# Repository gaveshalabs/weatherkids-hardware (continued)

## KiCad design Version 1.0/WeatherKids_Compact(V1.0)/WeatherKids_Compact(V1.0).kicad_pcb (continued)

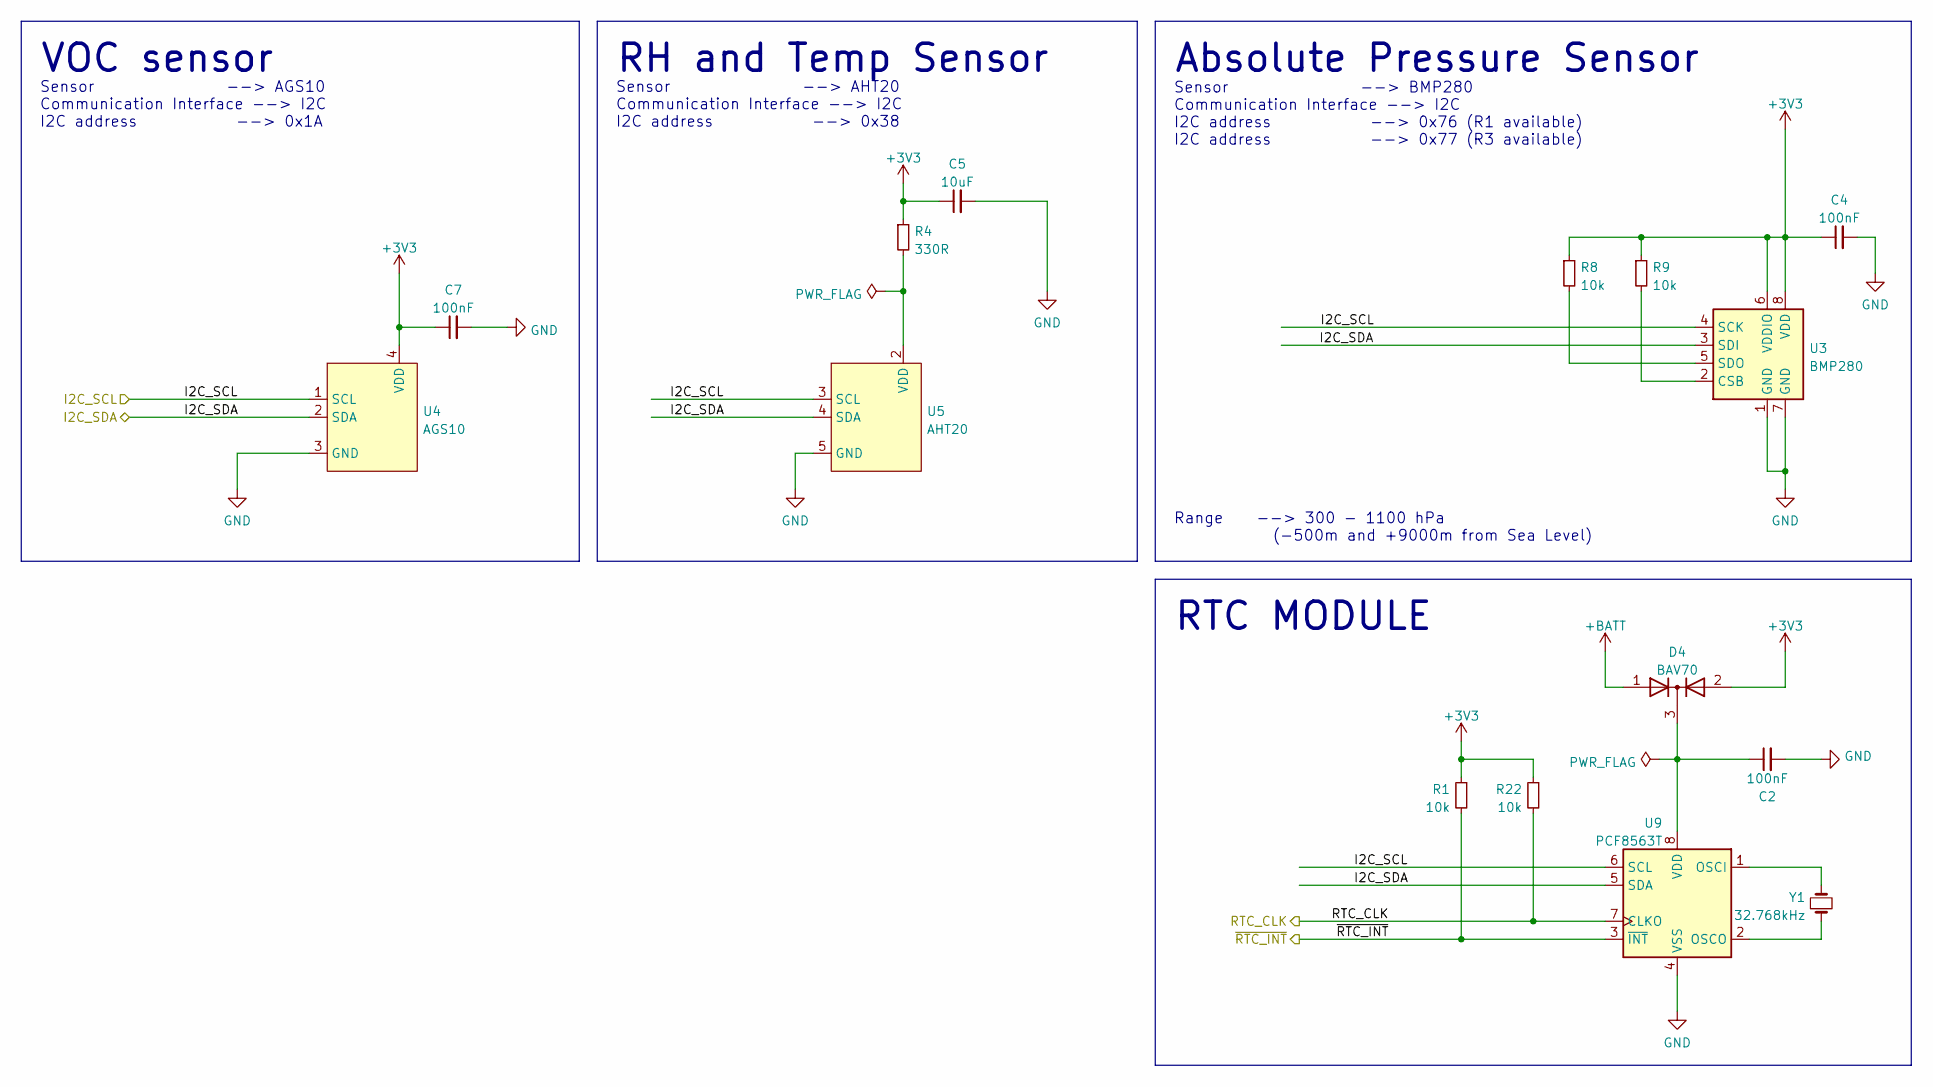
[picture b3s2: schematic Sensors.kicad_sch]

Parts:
C2, C4, C7: 100nF; C_0402_1005Metric
C5: 10uF; C_0805_2012Metric
D4: BAV70; SOT-23
R1, R8, R9, R22: 10k; R_0402_1005Metric
R4: 330R; R_0402_1005Metric
U3: BMP280; Bosch_LGA-8_2x2.5mm_P0.65mm_ClockwisePinNumbering
U4: AGS10
U5: AHT20
U9: PCF8563T; SOIC-8_3.9x4.9mm_P1.27mm
Y1: 32.768kHz; Crystal_SMD_3215-2Pin_3.2x1.5mm

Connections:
+3V3: C4.1, C5.1, C7.1, D4.2 (A), R1.1, R4.1, R8.1, R9.1, R22.1, U3.6 (VDDIO), U3.8 (VDD), U4.4 (VDD); also elsewhere on the board
+BATT: D4.1 (A); also elsewhere on the board
/Environment Sensors/RTC_CLK: R22.2, U9.7 (CLKO); also elsewhere on the board
/Environment Sensors/~RTC_INT: R1.2, U9.3 (~INT); also elsewhere on the board
/I2C_SCL: U3.4 (SCK), U4.1 (SCL), U5.3 (SCL), U9.6 (SCL); also elsewhere on the board
/I2C_SDA: U3.3 (SDI), U4.2 (SDA), U5.4 (SDA), U9.5 (SDA); also elsewhere on the board
GND: C2.2, C4.2, C5.2, C7.2, U3.1 (GND), U3.7 (GND), U4.3 (GND), U5.5 (GND), U9.4 (VSS); also elsewhere on the board
unnamed: C2.1, D4.3 (K), U9.8 (VDD)
unnamed: R4.2, U5.2 (VDD)
unnamed: R8.2, U3.5 (SDO)
unnamed: R9.2, U3.2 (CSB)
unnamed: U9.1 (OSCI), Y1.2
unnamed: U9.2 (OSCO), Y1.1

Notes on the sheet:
Sensor --> AGS10 Communication Interface --> I2C I2C address --> 0x1A
Sensor --> BMP280 Communication Interface --> I2C I2C address --> 0x76 (R1 available) I2C address --> 0x77 (R3 available)
Range --> 300 - 1100 hPa (-500m and +9000m from Sea Level)
RH and Temp Sensor
RTC MODULE
Sensor --> AHT20 Communication Interface --> I2C I2C address --> 0x38
VOC sensor
Absolute Pressure Sensor

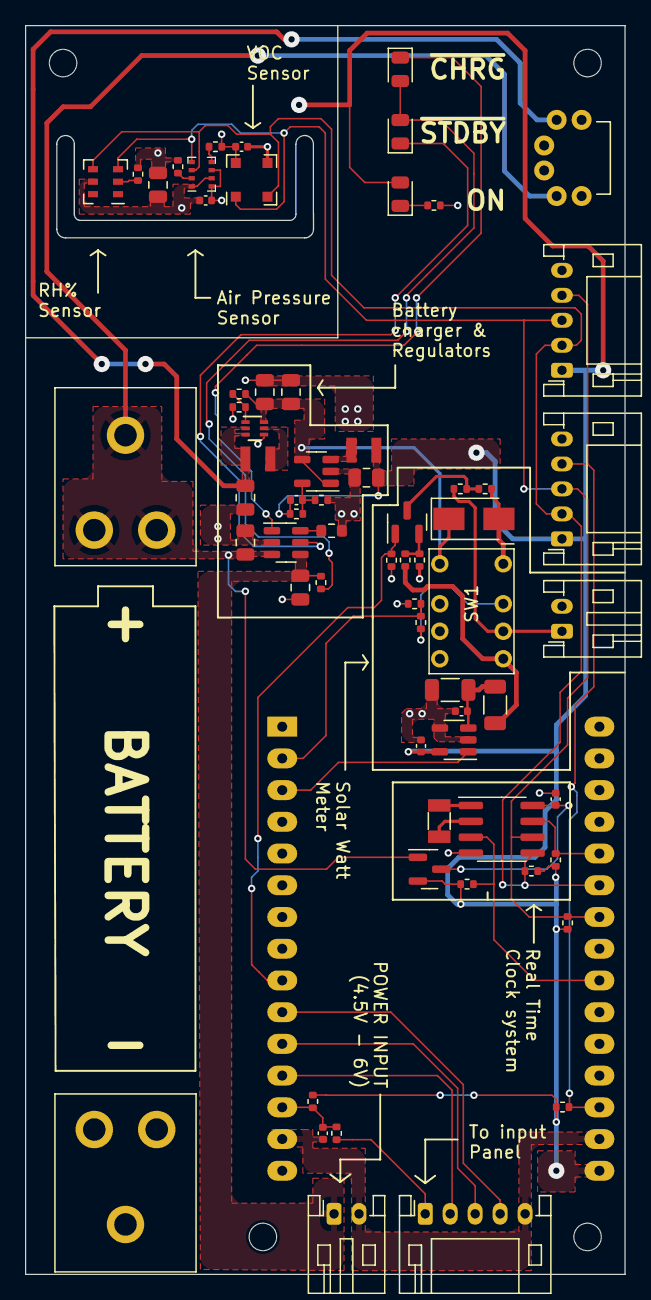
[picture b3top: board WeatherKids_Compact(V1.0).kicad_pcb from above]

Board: 2 copper layers, 48.0 x 100.0 mm, 71 parts (0 on the bottom side), 41 nets.

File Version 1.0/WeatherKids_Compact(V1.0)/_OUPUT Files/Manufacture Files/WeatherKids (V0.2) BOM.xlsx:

Index | Availability | Checked | Layer | Special Notes |  | Value | Footprint |  | JLC Basic Part Match | JLCPCBA part | LCSC Part Number | Manufacturer Part Number | Manufacture | Unit Price | Total
1 | YES |  |  |  | C2, C3, C4, C6, C7, C9 | 100nF | Capacitor_SMD:C_0402_1005Metric | 6 | Y | C1525 | C60474 | CC0402KRX7R7BB104 |  | 8.0000000000000004E-4 | 4.8000000000000004E-3
2 | YES |  |  |  | C10 | 12pF | Capacitor_SMD:C_0402_1005Metric | 1 | Y | C1547 | C106201 | CC0402JRNPO9BN120 |  | 1E-3 | 1E-3
3 | YES |  |  |  | C5, C8, C11, C12, C13, C15, C16 | 10uF | Capacitor_SMD:C_0805_2012Metric | 7 | Y | C15850 | C89827 | CC0805KKX5R7BB106 |  | 2.75E-2 | 0.1925
4 | YES |  |  |  | D6 | SS34 | Diode_SMD:D_SMA | 1 | Y | C8678 | C8678 | SS34 |  | 2.7799999999999998E-2 | 2.7799999999999998E-2
5 | YES |  |  |  | D4 | BAV70 | Package_TO_SOT_SMD:SOT-23 | 1 | Y | C68978 | C68978 | BAV70 |  | 1.8499999999999999E-2 | 1.8499999999999999E-2
6 | YES |  |  |  | D1, D2, D5 | LED | LED_SMD:LED_0805_2012Metric | 3 | Y | C34499 | C34499 | C34499 | Hubei KENTO Elec | 1.5699999999999999E-2 | 4.7099999999999996E-2
7 | YES |  |  |  | J1, J2, J3 | Conn_01x05 | Connector_JST:JST_PH_S5B-PH-K_1x05_P2.00mm_Horizontal | 3 | N | C10402 | C442192 | HX20007-5WAD |  | 3.0499999999999999E-2 | 9.1499999999999998E-2
8 | YES |  |  |  | J4, J5 | Conn_01x02 | Connector_JST:JST_PH_S2B-PH-K_1x02_P2.00mm_Horizontal | 2 | N | C16965 | C16965 | PH-2AW |  | 5.5999999999999999E-3 | 1.12E-2
 | YES |  |  |  | J6, J7 | CONN1X15 | 2.54 Female connector | 2 | N | C124408 | C124408 | B-2200S15P-A120 |  | 0.15179999999999999 | 0.30359999999999998
9 | YES |  |  |  | J9, J10 | MY-18650-01 | Myoung:MY-18650-01 | 2 | N | C2979183 | C2979183 | MY-18650-01 |  | 0.30520000000000003 | 0.61040000000000005
10 | YES |  |  |  | L1 | 1uH | Inductor_SMD:L_Taiyo-Yuden_NR-20xx | 1 | N | C279952 | C279952 | WPN252010U1R0MT |  | 5.7200000000000001E-2 | 5.7200000000000001E-2
11 | YES |  |  |  | L2 | 2.2uH | Sunlord Inductors:WPN252010U | 1 | N | C279871 | C279871 | WPN252010U2R2MT |  | 5.1700000000000003E-2 | 5.1700000000000003E-2
12 | YES |  |  |  | Q1 | AO3400A | Package_TO_SOT_SMD:SOT-23 | 1 | Y | C20917 | C20917 | AO3400A |  | 7.9000000000000001E-2 | 7.9000000000000001E-2
13 | YES |  |  |  | R2 | 1R | Resistor_SMD:R_1206_3216Metric | 1 | Y | C17928 | C17928 | 1206W4F100KT5E |  | 4.4000000000000003E-3 | 4.4000000000000003E-3
14 | YES |  |  |  | R4, R14, R25 | 330R | Resistor_SMD:R_0402_1005Metric | 1 | Y | C25104 | C25104 | 0402WGF3300TCE |  | 5.0000000000000001E-4 | 5.0000000000000001E-4
15 | YES |  |  |  | R5, R23, R24 | 4.7k | Resistor_SMD:R_0402_1005Metric | 3 | Y | C25900 | C25900 | 0402WGF4701TCE |  | 5.9999999999999995E-4 | 1.8E-3
16 | YES |  |  |  | R3, R6, R7, R10 | 0R | Resistor_SMD:R_0402_1005Metric | 4 | Y | C17168 | C17168 | 0402WGF0000TCE |  | 5.0000000000000001E-4 | 2E-3
17 | YES |  |  |  | R1, R8, R9, R11, R15, R22 | 10k | Resistor_SMD:R_0402_1005Metric | 6 | Y | C25744 | C60490 | RC0402FR-0710KL |  | 5.0000000000000001E-4 | 3.0000000000000001E-3
18 | YES |  |  |  | R16 | 1k | Resistor_SMD:R_0402_1005Metric | 1 | Y | C11702 | C11702 | 0402WGF1001TCE |  | 5.0000000000000001E-4 | 5.0000000000000001E-4
19 | YES |  |  |  | R17 | 2k | Resistor_SMD:R_0603_1608Metric | 1 | y | C4109 | C4109 | 0402WGF2001TCE |  | 5.0000000000000001E-4 | 5.0000000000000001E-4
20 | YES |  |  |  | R12, R13, R18 | 100k | Resistor_SMD:R_0402_1005Metric | 3 | y | C25741 | C25741 | 0402WGF1003TCE |  | 5.0000000000000001E-4 | 1.5E-3
21 | YES |  |  |  | R19 | 510k | Resistor_SMD:R_0402_1005Metric | 1 | y | C11616 | C11616 | 0402WGF5103TCE |  | 5.9999999999999995E-4 | 5.9999999999999995E-4
22 | YES |  |  |  | R20 | 22k | Resistor_SMD:R_0402_1005Metric | 1 | Y | C25768 | C25768 | 0402WGF2202TCE |  | 5.0000000000000001E-4 | 5.0000000000000001E-4
23 | YES |  |  |  | R26 | 100R | Resistor_SMD:R_1206_3216Metric | 1 | Y | C17901 | C17901 | 1206W4F1000T5E |  | 2.8999999999999998E-3 | 2.8999999999999998E-3
24 | YES |  |  |  | R21 | 68k | Resistor_SMD:R_0402_1005Metric | 1 | y | C36871 | C36871 | 0402WGF6802TCE |  | 5.9999999999999995E-4 | 5.9999999999999995E-4
25 | YES |  |  |  | SW1 | HFD4_5S | Xiamen_Hiongfa:HDF4 | 1 | N | C23510 | C23510 | HFD4/5 |  | 1.0077 | 1.0077
26 | YES |  |  |  | SW2 | SW_SPST | XKB:XKB5858-X-E | 1 | N | C780038 | C780038 | XKB5858-Z-E |  | 0.21479999999999999 | 0.21479999999999999
27 | YES |  |  |  | U2 | INA180A2 | Package_TO_SOT_SMD:SOT-23-5 | 1 | N | C192764 | C192764 | INA180A2IDBVR |  | 0.25740000000000002 | 0.25740000000000002
28 | YES |  |  |  | U3 | BMP280 | Package_LGA:Bosch_LGA-8_2x2.5mm_P0.65mm_ClockwisePinNumbering | 1 | N | C83291 | C83291 | BMP280 |  | 1.5547 | 1.5547
29 | YES |  |  |  | U4 | AGS10 | ASAIR Sensors:AGS10 | 1 | N | C3012632 | C3012632 | AGS10 |  | 1.4497 | 1.4497
30 | YES |  |  |  | U5 | AHT20 | ASAIR Sensors:AHT20 | 1 | N | C3012622 | C3012622 | AHT20-F |  | 0.70369999999999999 | 0.70369999999999999
31 | YES |  |  |  | U6 | TP4057 | Package_TO_SOT_SMD:SOT-23-6 | 1 | N | C12044 | C12044 | TP4057-42-SOT26-R |  | 0.12809999999999999 | 0.12809999999999999
32 | YES |  |  |  | U7 | RT8059GJ5 | Package_TO_SOT_SMD:TSOT-23-5 | 1 | N | C20542 | C20542 | RT5796CHGJ5 |  | 0.2 | 0.2
33 | YES |  |  |  | U1 | TPS61023DRL | Texas_Instruments:DRL0006A | 1 | N | C919459 | C919459 | TPS61023DRLR |  | 0.27700000000000002 | 0.27700000000000002
34 | YES |  |  |  | U9 | PCF8563T | Package_SO:SOIC-8_3.9x4.9mm_P1.27mm | 1 | Y | C7440 | C7440 | PCF8563T/5,518 |  | 0.5877 | 0.5877
35 | YES |  |  |  | Y1 | 32.768kHz | Crystal:Crystal_SMD_3215-2Pin_3.2x1.5mm | 1 | Y | C32346 | C32346 | Q13FC1350000400 |  | 0.1978 | 0.1978
36 | YES |  | NA | ESP32 DevKit | MOD1 | ESP32_DEVKIT_V1 | Espressif_Systems:ESP32_DEVKIT_V1.0 | 1 | N |  |  | ESP32_DEVKIT_V1 |  | 3.9473684210526314 | 3.9473684210526314
37 | YES |  | NA | 1800 mAh Batter | Battery | Batttery | Li-ion battery | 1 | N |  |  | Batttery |  | 1.5 | 1.5
38 | YES |  | NA | 2 Layer PCB Cost | PCB |  |  | 1 | N |  |  |  |  | 0.51 | 0.51
39 | YES |  | NA | Soldering (single side) | Assembly Fee |  |  | 1 | N |  |  |  |  | 2.2999999999999998 | 2.2999999999999998
40 | YES |  | NA | 3D printed casing | Casing |  |  | 1 | N |  |  |  |  | 3 | 3
41 | YES |  | NA | Shipping cost from china to Sri Lanka | Direct Shipping cost |  |  | 1 | N |  |  |  |  | 3.5 | 3.5
42 | YES |  |  |  | H1-H4 | Screws |  | 4 | N
 |  |  |  |  |  |  |  |  |  |  |  |  | Total without Tax |  | 22.851068421052631
 |  |  |  |  |  |  |  |  |  |  |  |  | Total with Tax |  | 24.679153894736842
 |  |  |  |  |  |  |  |  |  |  |  |  | Total with 10% error Margine |  | 27.147069284210527
 |  |  |  |  |  |  |  |  |  |  |  |  | Final Cost (LKR) |  | 10315.886328000001

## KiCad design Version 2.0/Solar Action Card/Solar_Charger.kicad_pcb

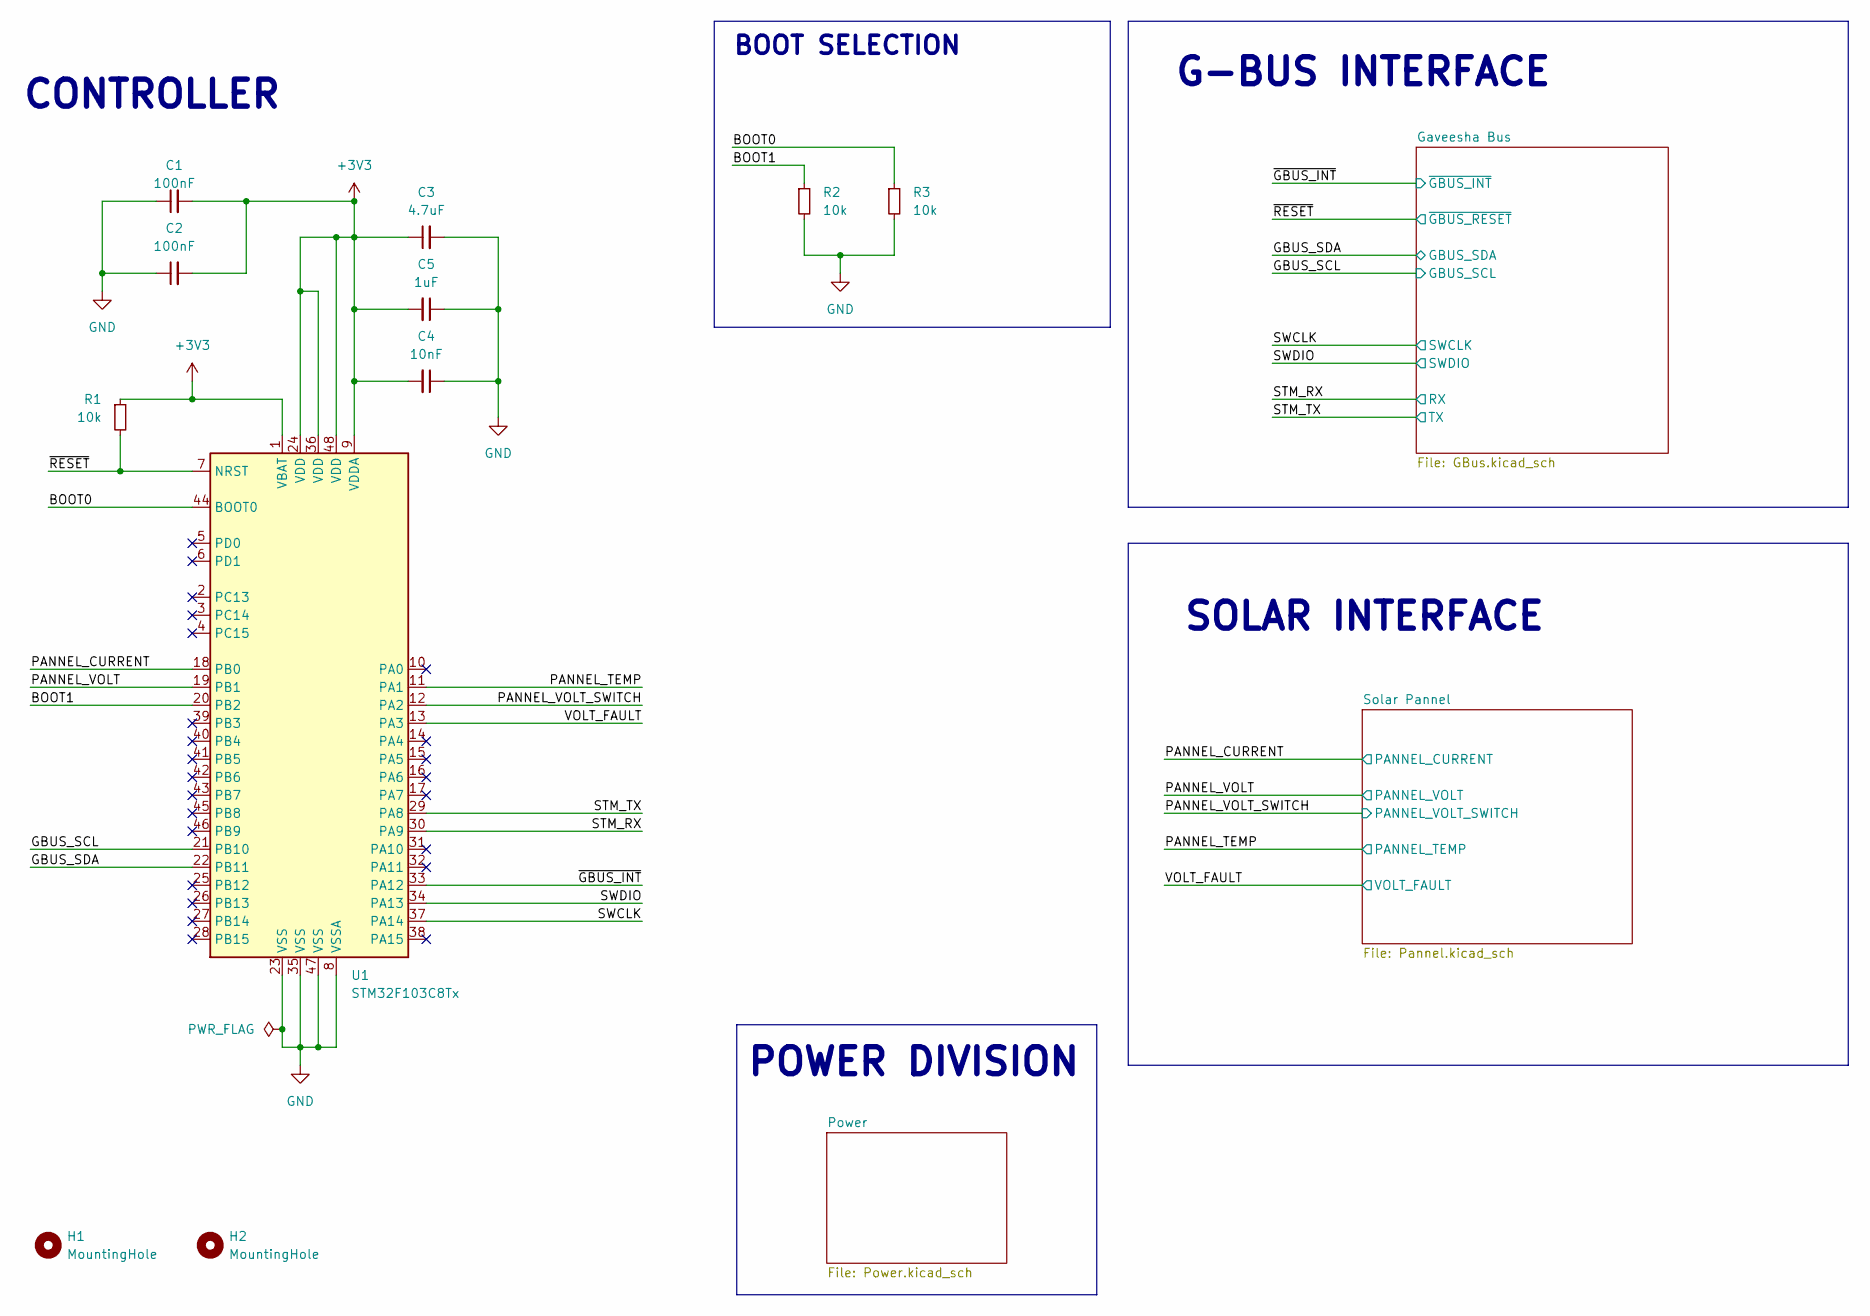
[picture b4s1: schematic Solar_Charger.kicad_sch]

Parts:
C1, C2: 100nF; C_0603_1608Metric; JLC PCB Part No. C1525
C3: 4.7uF; C_0402_1005Metric; JLC PCB Part No C23733
C4: 10nF; C_0402_1005Metric; JLC PCB Part No. C15195
C5: 1uF; C_0402_1005Metric; JLC PCB Part No. C52923
H1, H2: MountingHole; MountingHole_2.2mm_M2
R1, R2, R3: 10k; R_0402_1005Metric
U1: STM32F103C8Tx; LQFP-48_7x7mm_P0.5mm

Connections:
+3V3: C1.2, C2.2, C3.1, C4.2, C5.2, R1.1, U1.1 (VBAT), U1.9 (VDDA), U1.24 (VDD), U1.36 (VDD), U1.48 (VDD); also elsewhere on the board
/BOOT0: R3.1, U1.44 (BOOT0)
/BOOT1: R2.1, U1.20 (PB2)
/GBUS_SCL: U1.21 (PB10); also elsewhere on the board
/GBUS_SDA: U1.22 (PB11); also elsewhere on the board
/PANNEL_CURRENT: U1.18 (PB0); also elsewhere on the board
/PANNEL_TEMP: U1.11 (PA1); also elsewhere on the board
/PANNEL_VOLT: U1.19 (PB1); also elsewhere on the board
/PANNEL_VOLT_SWITCH: U1.12 (PA2); also elsewhere on the board
/STM_RX: U1.30 (PA9); also elsewhere on the board
/STM_TX: U1.29 (PA8); also elsewhere on the board
/SWCLK: U1.37 (PA14); also elsewhere on the board
/SWDIO: U1.34 (PA13); also elsewhere on the board
/VOLT_FAULT: U1.13 (PA3); also elsewhere on the board
/~GBUS_INT: U1.33 (PA12); also elsewhere on the board
/~RESET: R1.2, U1.7 (NRST); also elsewhere on the board
GND: C1.1, C2.1, C3.2, C4.1, C5.1, R2.2, R3.2, U1.8 (VSSA), U1.23 (VSS), U1.35 (VSS), U1.47 (VSS); also elsewhere on the board

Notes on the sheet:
CONTROLLER
BOOT SELECTION
POWER DIVISION
SOLAR INTERFACE
G-BUS INTERFACE

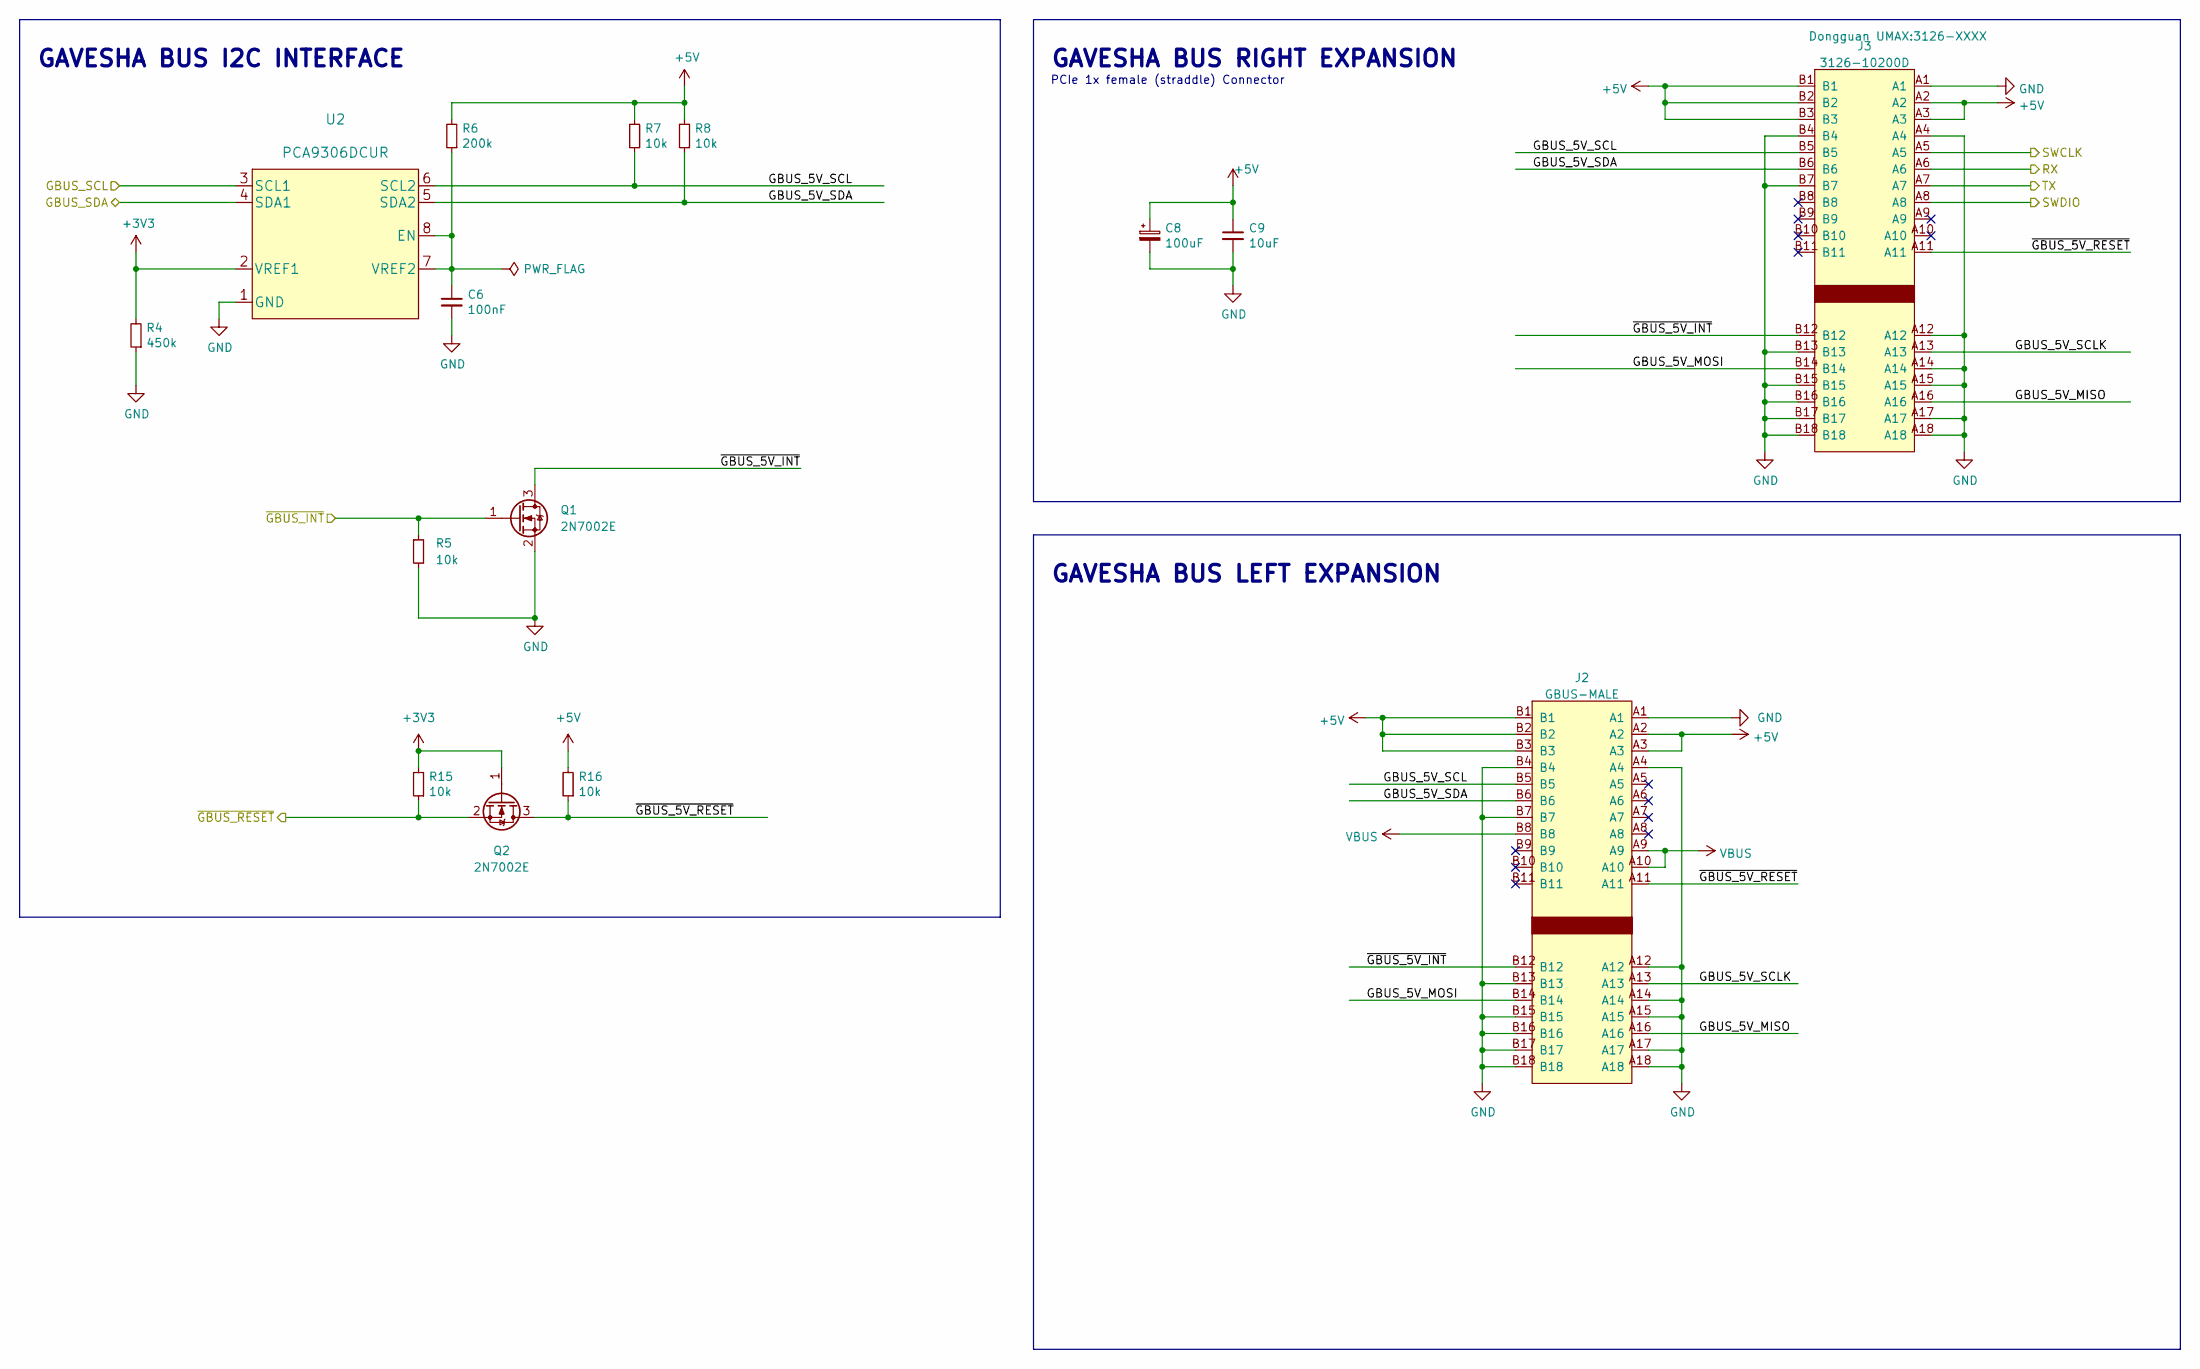
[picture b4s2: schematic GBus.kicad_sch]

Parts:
C6: 100nF; C_0402_1005Metric
C8: 100uF; CP_EIA-3528-12_Kemet-T
C9: 10uF; C_0805_2012Metric
J2: GBUS-MALE; GBUS_MALE
J3: 3126-10200D; 3126-XXXX
Q1, Q2: 2N7002E; SOT-23
R4: 450k; R_0402_1005Metric
R5, R7, R8, R15, R16: 10k; R_0402_1005Metric
R6: 200k; R_0402_1005Metric
U2: PCA9306DCUR

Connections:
+3V3: Q2.1 (G), R4.2, R15.2, U2.2 (VREF1); also elsewhere on the board
+5V: C8.1, C9.1, J2.A2, J2.A3, J2.B1, J2.B2, J2.B3, J3.A2, J3.A3, J3.B1, J3.B2, J3.B3, R6.2, R7.2, R8.2, R16.2; also elsewhere on the board
/GBUS_SCL: U2.3 (SCL1); also elsewhere on the board
/GBUS_SDA: U2.4 (SDA1); also elsewhere on the board
/Gaveesha Bus/GBUS_5V_MISO: J2.A16, J3.A16
/Gaveesha Bus/GBUS_5V_MOSI: J2.B14, J3.B14
/Gaveesha Bus/GBUS_5V_SCL: J2.B5, J3.B5, R7.1, U2.6 (SCL2)
/Gaveesha Bus/GBUS_5V_SCLK: J2.A13, J3.A13
/Gaveesha Bus/GBUS_5V_SDA: J2.B6, J3.B6, R8.1, U2.5 (SDA2)
/Gaveesha Bus/~GBUS_5V_INT: J2.B12, J3.B12, Q1.3 (D)
/Gaveesha Bus/~GBUS_5V_RESET: J2.A11, J3.A11, Q2.3 (D), R16.1
/STM_RX: J3.A6; also elsewhere on the board
/STM_TX: J3.A7; also elsewhere on the board
/SWCLK: J3.A5; also elsewhere on the board
/SWDIO: J3.A8; also elsewhere on the board
/~GBUS_INT: Q1.1 (G), R5.1; also elsewhere on the board
/~RESET: Q2.2 (S), R15.1; also elsewhere on the board
GND: C6.2, C8.2, C9.2, J2.A1, J2.A4, J2.A12, J2.A14, J2.A15, J2.A17, J2.A18, J2.B4, J2.B7, J2.B13, J2.B15, J2.B16, J2.B17, J2.B18, J3.A1, J3.A4, J3.A12, J3.A14, J3.A15, J3.A17, J3.A18, J3.B4, J3.B7, J3.B13, J3.B15, J3.B16, J3.B17, J3.B18, Q1.2 (S), R4.1, R5.2, U2.1 (GND); also elsewhere on the board
unnamed: C6.1, R6.1, U2.7 (VREF2), U2.8 (EN)
VBUS: J2.A9, J2.A10, J2.B8; also elsewhere on the board

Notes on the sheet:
PCIe 1x female (straddle) Connector
GAVESHA BUS LEFT EXPANSION
GAVESHA BUS I2C INTERFACE
GAVESHA BUS RIGHT EXPANSION

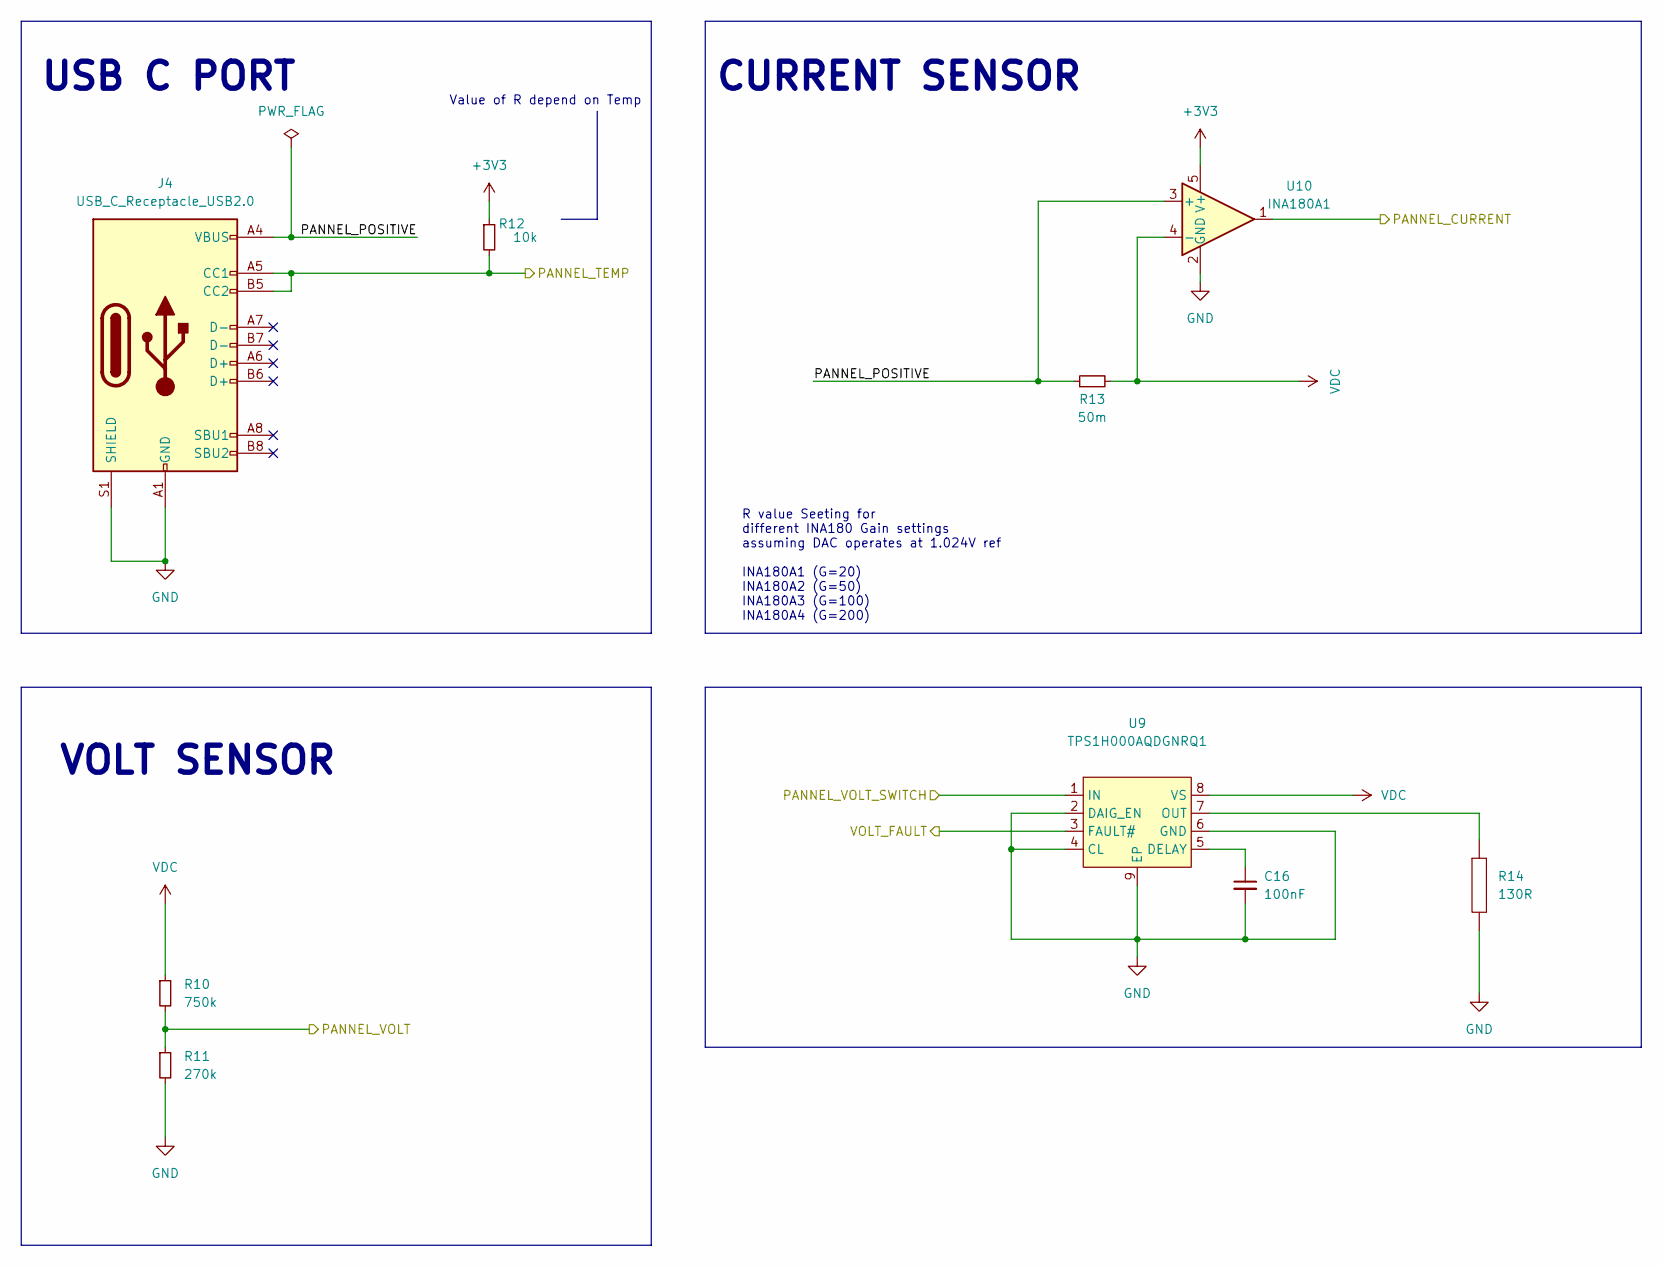
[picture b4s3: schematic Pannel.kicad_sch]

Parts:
C16: 100nF; R_0603_1608Metric
J4: USB_C_Receptacle_USB2.0; USB_C_Receptacle_HRO_TYPE-C-31-M-12
R10: 750k; R_0603_1608Metric
R11: 270k; R_0603_1608Metric
R12: 10k; R_0603_1608Metric
R13: 50m; R_1206_3216Metric; LCSC Part# C912768
R14: 130R; R_Axial_DIN0516_L15.5mm_D5.0mm_P20.32mm_Horizontal; LCSC part# C119572
U9: TPS1H000AQDGNRQ1; MSOP-8-1EP_3x3mm_P0.65mm_EP1.95x2.15mm
U10: INA180A1; SOT-23-5

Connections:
+3V3: R12.1, U10.5 (V+); also elsewhere on the board
/PANNEL_CURRENT: U10.1; also elsewhere on the board
/PANNEL_TEMP: J4.A5 (CC1), J4.B5 (CC2), R12.2; also elsewhere on the board
/PANNEL_VOLT: R10.2, R11.1; also elsewhere on the board
/PANNEL_VOLT_SWITCH: U9.1 (IN); also elsewhere on the board
/Solar Pannel/PANNEL_POSITIVE: J4.A4 (VBUS), J4.A9 (VBUS), J4.B4 (VBUS), J4.B9 (VBUS), R13.1, U10.3 (+)
/VOLT_FAULT: U9.3 (FAULT#); also elsewhere on the board
GND: C16.2, J4.A1 (GND), J4.A12 (GND), J4.B1 (GND), J4.B12 (GND), J4.S1 (SHIELD), R11.2, R14.2, U9.2 (DAIG_EN), U9.4 (CL), U9.6 (GND), U9.9 (EP), U10.2 (GND); also elsewhere on the board
unnamed: C16.1, U9.5 (DELAY)
unnamed: R14.1, U9.7 (OUT)
VDC: R10.1, R13.2, U9.8 (VS), U10.4 (-); also elsewhere on the board

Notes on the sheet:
Value of R depend on Temp
CURRENT SENSOR
VOLT SENSOR
USB C PORT
R value Seeting for different INA180 Gain settings assuming DAC operates at 1.024V ref INA180A1 (G=20) INA180A2 (G=50) INA180A3 (G=100) INA180A4 (G=200)

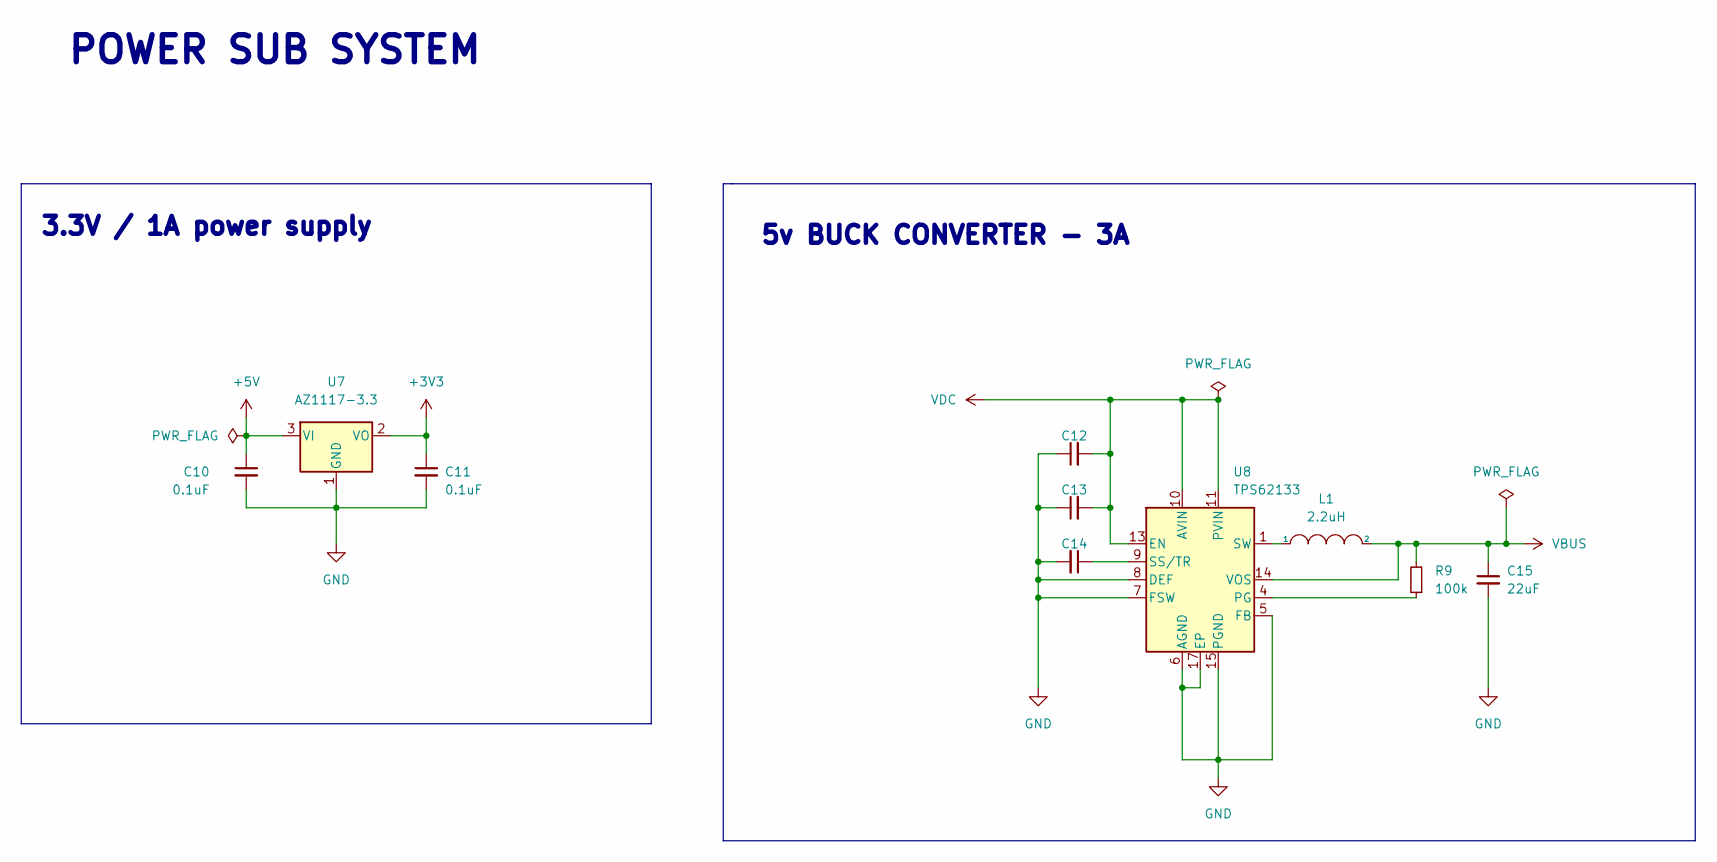
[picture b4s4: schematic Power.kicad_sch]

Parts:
C10: 0.1uF; C_0603_1608Metric
C11: 0.1uF; C_0805_2012Metric
C12: 10uF; C_0402_1005Metric
C13: 100nF; C_0402_1005Metric
C14: 3.3nF; C_0402_1005Metric
C15: 22uF; C_0603_1608Metric
L1: 2.2uH; L_Sunlord_MWSA0518_5.4x5.2mm; LCSC C408345
R9: 100k; R_0402_1005Metric
U7: AZ1117-3.3; SOT-223
U8: TPS62133; VQFN-16-1EP_3x3mm_P0.5mm_EP1.68x1.68mm_ThermalVias; LCSC C2653764

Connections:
+3V3: C11.1, U7.2 (VO); also elsewhere on the board
+5V: C10.1, U7.3 (VI); also elsewhere on the board
GND: C10.2, C11.2, C12.1, C13.1, C14.2, C15.2, U7.1 (GND), U8.5 (FB), U8.6 (AGND), U8.7 (FSW), U8.8 (DEF), U8.15 (PGND), U8.16 (PGND), U8.17 (EP); also elsewhere on the board
unnamed: C14.1, U8.9 (SS/TR)
unnamed: L1.1, U8.1 (SW), U8.2 (SW), U8.3 (SW)
unnamed: R9.1, U8.4 (PG)
VBUS: C15.1, L1.2, R9.2, U8.14 (VOS); also elsewhere on the board
VDC: C12.2, C13.2, U8.10 (AVIN), U8.11 (PVIN), U8.12 (PVIN), U8.13 (EN); also elsewhere on the board

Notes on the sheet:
POWER SUB SYSTEM
5v BUCK CONVERTER - 3A
3.3V / 1A power supply

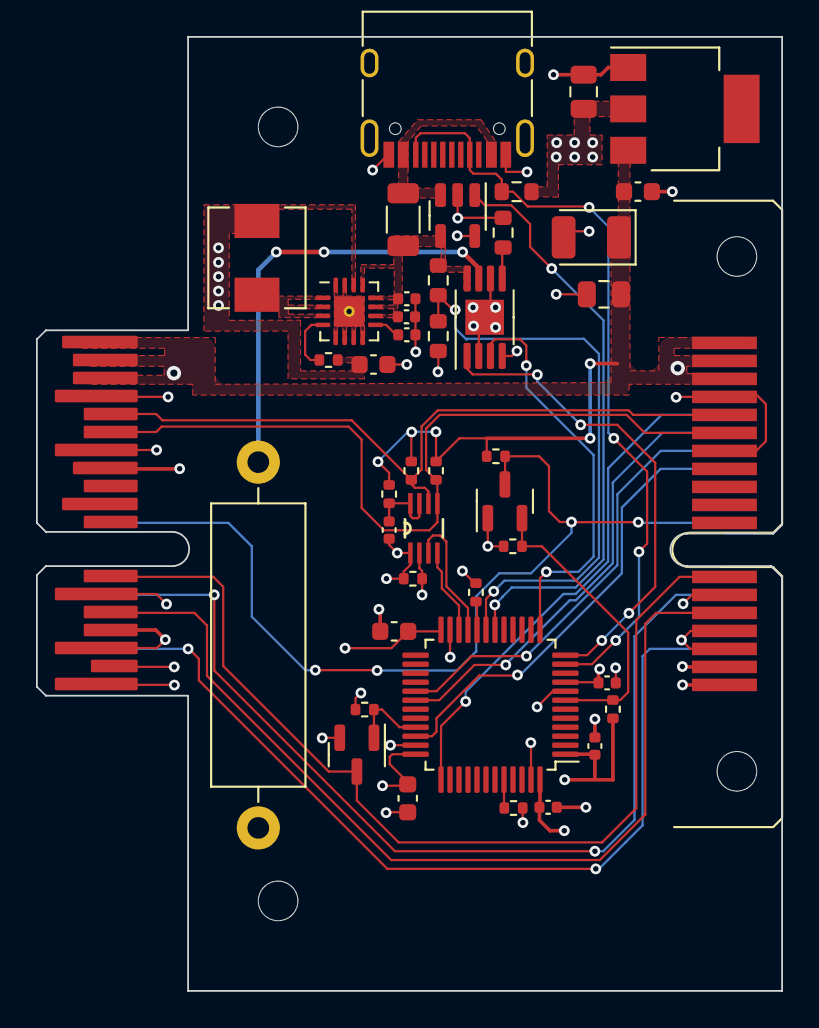
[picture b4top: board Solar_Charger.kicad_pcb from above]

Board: 2 copper layers, 41.4 x 53.0 mm, 45 parts (0 on the bottom side), 34 nets.

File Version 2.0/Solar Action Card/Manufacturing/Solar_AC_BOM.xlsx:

C14663 | Footprint | Quantity | Value | LCSC Part #
C1, C16, C2, C10, C11, C13, C6 | 603 | 7 | 100nF | C14663
C12 | 603 | 1 | 10uF | C96446
C14 | 603 | 1 | 3.3nF | C1613
C15 | 603 | 1 | 22uF | C59461
C3 | 402 | 1 | 4.7uF | C23733
C4 | 402 | 1 | 10nF | C15195
C5 | 402 | 1 | 1uF | C52923
C8 | CP_EIA-3528-12_Kemet-T | 1 | 100uF | C16133
C9 | 805 | 1 | 10uF | C15850
J4 | USB_C_Receptacle_HRO_TYPE-C-31-M-12 | 1 | USB_C_Receptacle_USB2.0 | C165948
L1 | L_Sunlord_MWSA0518_5.4x5.2mm | 1 | 2.2uH | C408345
Q1, Q2 | SOT-23 | 2 | 2N7002E | C8545
R1, R15, R16, R2, R3, R5, R7, R8, R12 | 402 | 9 | 10k | C25744
R10 | 603 | 1 | 750k | C441908
R11 | 603 | 1 | 270k | C2889163
R13 | 1206 | 1 | 50m | C912768
R14 | R_Axial_DIN0516_L15.5mm_D5.0mm_P20.32mm_Horizontal | 1 | 130R | C119572 |  | C5166557
R6 | 402 | 1 | 200k | C25764
R9 | 402 | 1 | 100k | C25741
U1 | LQFP-48_7x7mm_P0.5mm | 1 | STM32F103C8Tx | C8734
U10 | SOT-23-5 | 1 | INA180A1 | C122228
U2 | PCA9306DCUR | 1 | PCA9306DCUR | C33196
U7 | SOT-223 | 1 | AZ1117-3.3 | C6186
U8 | VQFN-16-1EP_3x3mm_P0.5mm_EP1.68x1.68mm_ThermalVias | 1 | TPS62133 | C73973
U9 | MSOP-8-1EP_3x3mm_P0.65mm_EP1.95x2.15mm | 1 | TPS1H000AQDGNRQ1 | C2653764
